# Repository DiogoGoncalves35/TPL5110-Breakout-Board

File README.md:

# Low Power TPL5110 Breakout Board

This small breakout board is designed arround the [TPL5110 Timer](https://www.ti.com/lit/ds/symlink/tpl5110.pdf?ts=1704823351945&ref_url=https%253A%252F%252Fwww.google.com%252F)

It's a very simple design, by soldering a THT resistor you can choose the time interval between cicles. 

With 5V power it only draws 50 nA while in standby. Measurements were done with [nrF Power Profiler Kit II](https://www.nordicsemi.com/Products/Development-hardware/Power-Profiler-Kit-2).

Circuit was tested with IRF9Z24N P-Channel Mosfet. It was added a 10k pull down resistor to the DONE pin for better stability, breadboard parasitic capacitance can cause noise on some lines. The mosfet controls the Arduino Uno board and after 10 seconds the Arduino sends a DONE signal to turn off.

------------

### Schematic

The [schematic](/PCB/Schematic.pdf) basicly exposes every pin to the connectors. A decoupling capacitor was added on the power rail. The resistor is responsible for the time period.

------------

### PCB

[This PCB](/PCB) has a very simple design, it's a 1.6 mm board with 2 copper layers, both connect to GND. 

------------

### Known issues

- Parasitic capacitance but it could be related to breadboard

------------

### To-Do

- No updates for now

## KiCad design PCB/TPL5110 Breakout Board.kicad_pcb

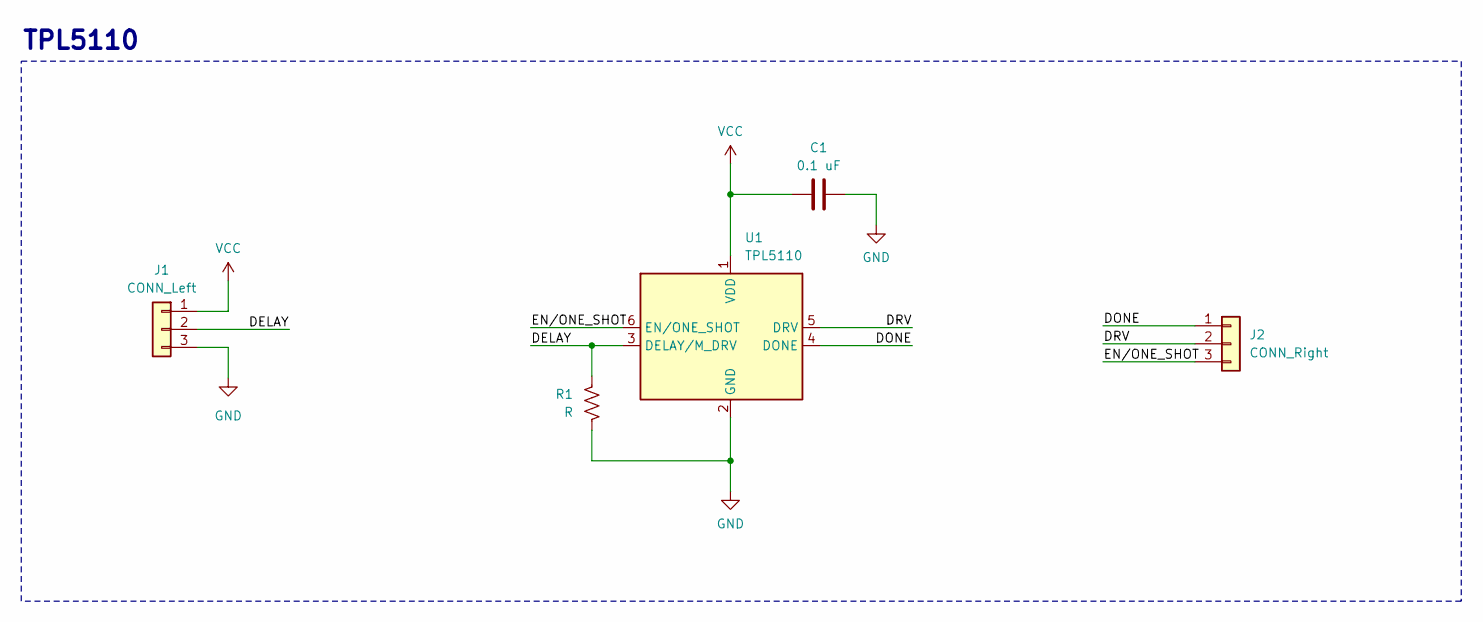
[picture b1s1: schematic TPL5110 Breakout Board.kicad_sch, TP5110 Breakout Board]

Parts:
C1: 0.1 uF; C_0603_1608Metric_Pad1.08x0.95mm_HandSolder; LCSC C14663
J1: CONN_Left; PinHeader_1x03_P2.54mm_Vertical
J2: CONN_Right; PinHeader_1x03_P2.54mm_Vertical
R1: R; R_Axial_DIN0204_L3.6mm_D1.6mm_P5.08mm_Horizontal
U1: TPL5110; SOT-23-6; LCSC C125830

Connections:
/DELAY: J1.2, R1.2, U1.3 (DELAY/M_DRV)
/DONE: J2.1, U1.4 (DONE)
/DRV: J2.2, U1.5 (DRV)
/EN/ONE_SHOT: J2.3, U1.6 (EN/ONE_SHOT)
GND: C1.1, J1.3, R1.1, U1.2 (GND)
VCC: C1.2, J1.1, U1.1 (VDD)

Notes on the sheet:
TPL5110

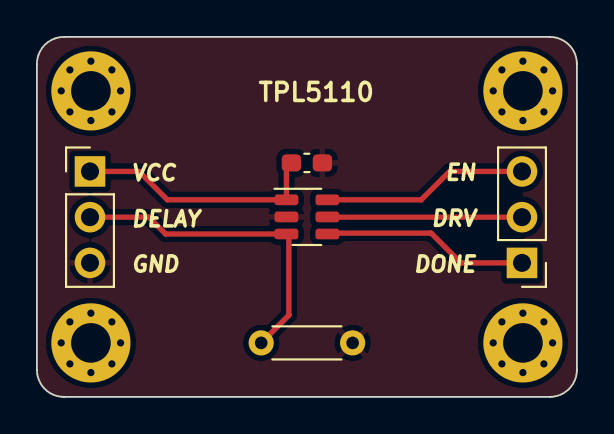
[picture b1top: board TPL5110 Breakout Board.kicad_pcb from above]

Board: 2 copper layers, 30.0 x 20.0 mm, 5 parts (0 on the bottom side), 6 nets.

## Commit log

2024-01-12 Schematic PDF
